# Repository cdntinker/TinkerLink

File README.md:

# Theory of operation:
* Power source is connected to USB1
  * can be populated with USB-C female or USB-A male
* USB2 can have its power turned on/off by the MCU using io12
  * can be populated with USB-C male or female
* D+ & D1, of course, pass right through
* When using USB-C on both ends, CC1 & CC2 are pased through (but swapped) and should allow for USB-PD capabilities
  * Also: R9 & R10 are there to add 5k1 resistors if needed.
    * Now the ESP handles inserting them via io2...
* LED1 is an RGB addressible LED (on io14) for status indication
  * RGBW now... Austin's fault... Blame Austin
* SW1 is on io13 of the MCU and can be used for local control

# Power Monitoring thoughts:
* INA chip selection
* The following are all drop-in replacements for each other...
  * INA228 (Current chip in the design)
    * very expensive
    * 625uA resoluation
  * INA237
    * 1/3 the price
    * 800uA resoluation
  * INA226
    * under a buck...
    * 1.5mA resoluation

# Firmware:
* Yet to be developped...
* Might work with TasmOTA like the original SiniLink could

# Notes:
Thanks to DJ_Dichotomy in the SuperHouseTV Discord for the antenna model...

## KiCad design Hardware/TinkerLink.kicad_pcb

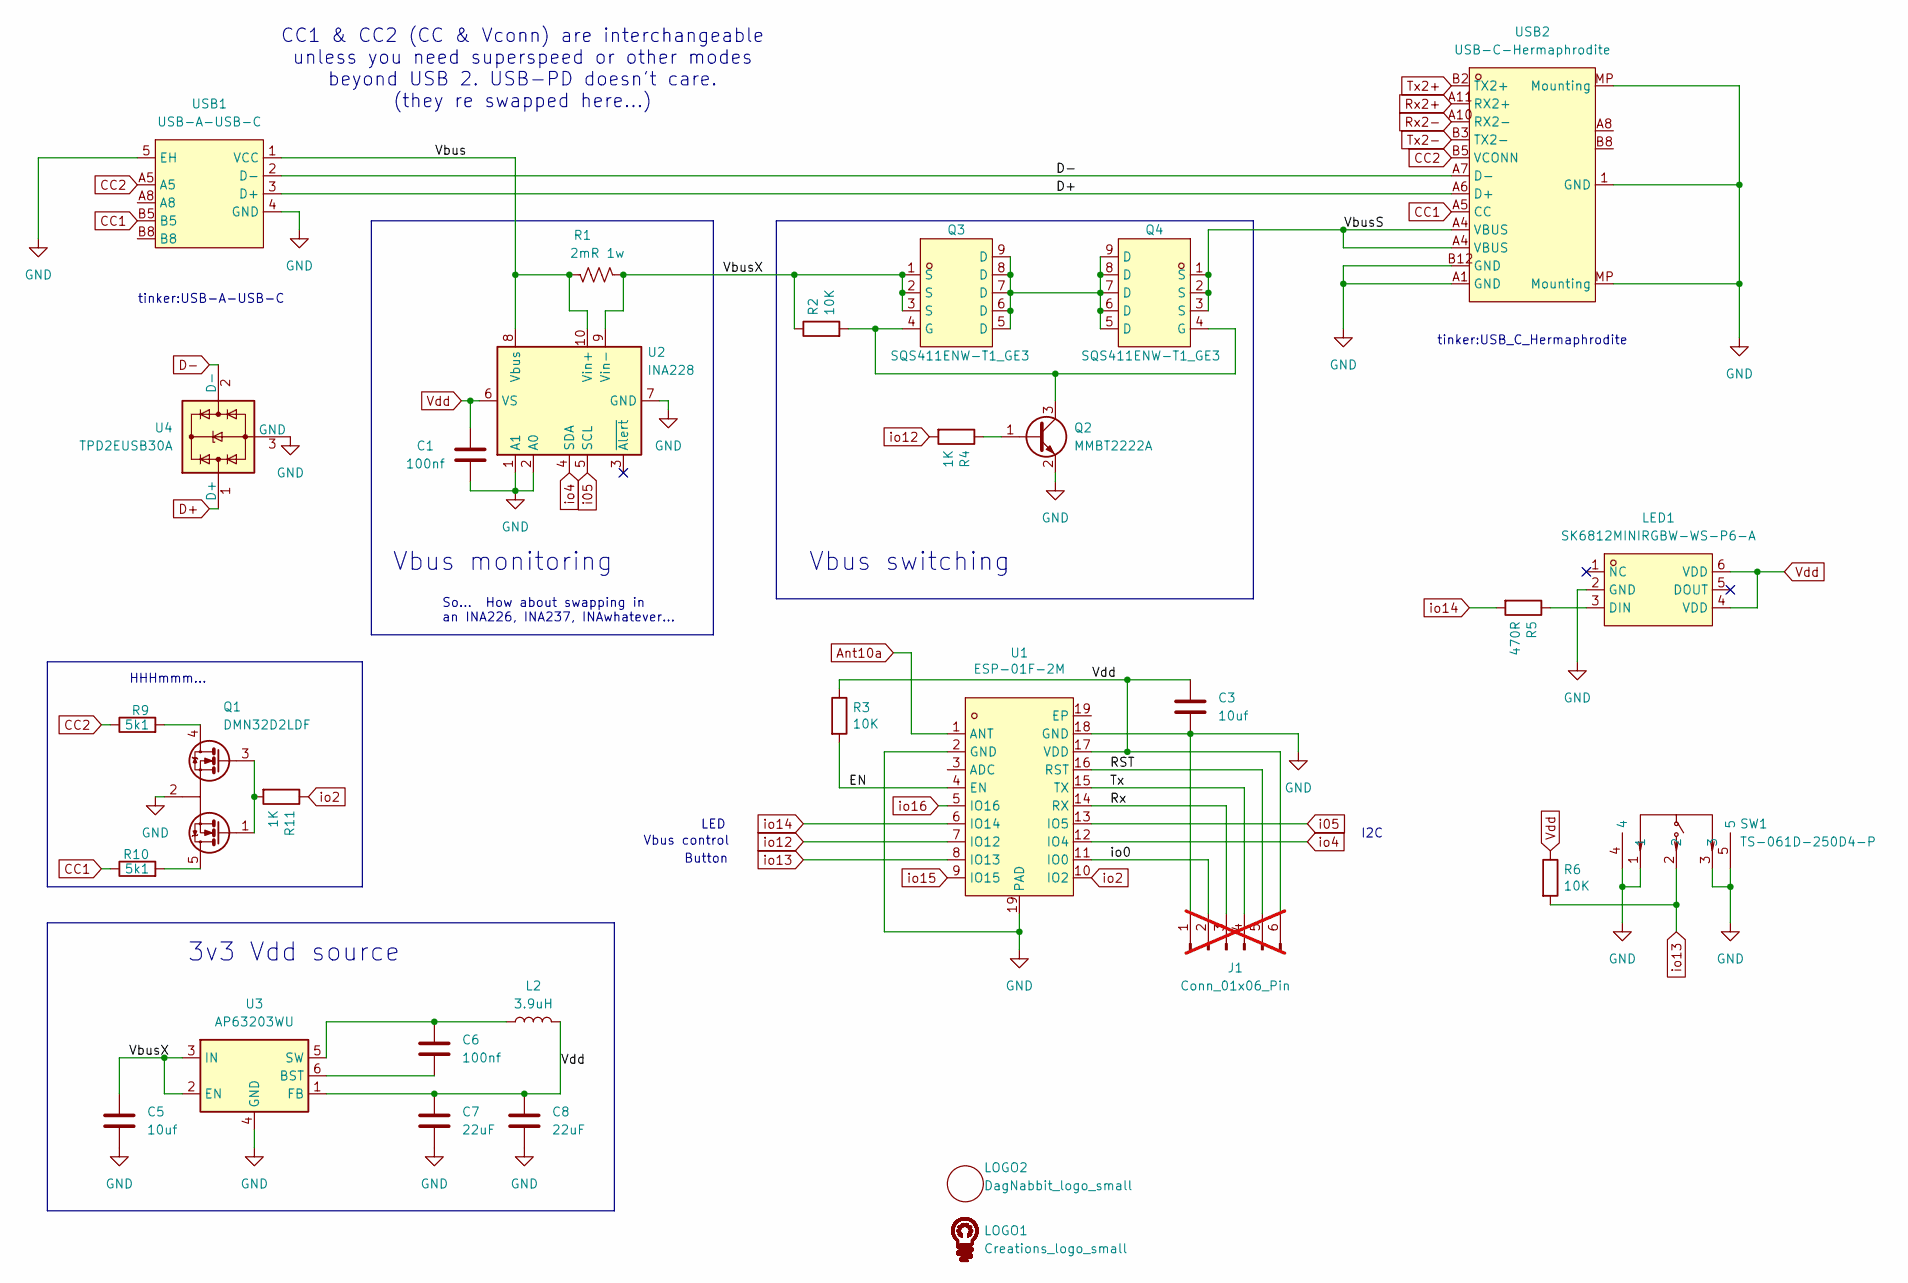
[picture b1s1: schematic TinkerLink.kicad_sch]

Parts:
C1: 100nf; C_0603_1608Metric; LCSC Part C14663
C3, C5: 10uf; C_0603_1608Metric; LCSC Part C19702
C6: 100nf; C_0603_1608Metric
C7, C8: 22uF; C_0603_1608Metric; LCSC Part C20416425
J1: Conn_01x06_Pin; ProgHeader_1x06_P2.00mm; not fitted
L2: 3.9uH; L_0603_1608Metric; LCSC Part C252079
LED1: SK6812MINIRGBW-WS-P6-A; LED-SMD_6P-L3.5-W3.5_SK6812MINIRGBW-WS-P6-A; MPN SK6812MINIRGBW-WS-P6-A; LCSC Part C7423106
LOGO1: Creations_logo_small; Creations logo small
LOGO2: DagNabbit_logo_small; DagNabbit
Q1: DMN32D2LDF; SOT-353_SC-70-5; LCSC Part C672154
Q2: MMBT2222A; SOT-23; LCSC Part C916372
Q3, Q4: SQS411ENW-T1_GE3; POWERPAK-1212-8_L3.1-W3.1-P0.65-LS3.3-BL; MPN SQS411ENW-T1_GE3; LCSC Part C3279469
R1: 2mR 1w; R_1206_3216Metric; LCSC Part C710257
R2, R3, R6: 10K; R_0603_1608Metric; LCSC Part C98220
R4, R11: 1K; R_0603_1608Metric; LCSC Part C22548
R5: 470R; R_0603_1608Metric; LCSC Part C114433
R9, R10: 5k1; R_0603_1608Metric; LCSC Part C23186
SW1: TS-061D-250D4-P; SW-SMD_K2-1847DT-A4SA-01; MPN TS-061D-250D4-P; LCSC Part C53207951
U1: ESP-01F-2M; ESP-01F; MPN ESP-01F-2M; LCSC Part C2764054
U2: INA228; VSSOP-10_3x3mm_P0.5mm; LCSC Part C2887910
U3: AP63203WU; TSOT-23-6; LCSC Part C780769
U4: TPD2EUSB30A; Texas_DRT-3; LCSC Part C3011197
USB1: USB-A-USB-C; MPN USB-212-BCW; LCSC Part C720521
USB2: USB-C-Hermaphrodite; USB_C_Hermaphrodite; MPN TYPE-C-31-G-10; LCSC Part C5370430

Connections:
/EN: R3.2, U1.4 (EN)
/RST: J1.5, U1.16 (RST)
/Rx: J1.3, U1.14 (RX)
/Tx: J1.4, U1.15 (TX)
/Vbus: R1.2, U2.8 (Vbus), U2.10 (Vin+), USB1.1 (VCC)
/VbusS: Q4.1 (S), Q4.2 (S), Q4.3 (S), USB2.A4 (VBUS)
/VbusX: C5.1, Q3.1 (S), Q3.2 (S), Q3.3 (S), R1.1, R2.1, U2.9 (Vin-), U3.2 (EN), U3.3 (IN)
/io0: J1.2, U1.11 (IO0)
Ant10a: U1.1 (ANT)
CC1: R10.1, USB1.B5, USB2.A5 (CC)
CC2: R9.1, USB1.A5, USB2.B5 (VCONN)
D+: U4.1 (D+), USB1.3 (D+), USB2.A6 (D+)
D-: U4.2 (D-), USB1.2 (D-), USB2.A7 (D-)
GND: C1.2, C3.2, C5.2, C7.2, C8.2, J1.1, LED1.2 (GND), Q1.2 (S), Q2.2 (E), SW1.1, SW1.3, SW1.4, SW1.5, U1.2 (GND), U1.18 (GND), U1.19 (PAD), U2.1 (A1), U2.2 (A0), U2.7 (GND), U3.4 (GND), U4.3 (GND), USB1.4 (GND), USB1.5 (EH), USB2.1 (GND), USB2.A1 (GND), USB2.B12 (GND), USB2.MP (Mounting)
unnamed: LED1.3 (DIN), R5.1
unnamed: Q1.5 (D1), R10.2
unnamed: Q1.4 (D2), R9.2
unnamed: Q1.1 (G1), Q1.3 (G2), R11.2
unnamed: Q2.1 (B), R4.1
unnamed: Q2.3 (C), Q3.4 (G), Q4.4 (G), R2.2
unnamed: Q3.5 (D), Q3.6 (D), Q3.7 (D), Q3.8 (D), Q3.9 (D), Q4.5 (D), Q4.6 (D), Q4.7 (D), Q4.8 (D), Q4.9 (D)
unnamed: C6.2, U3.6 (BST)
unnamed: C6.1, L2.1, U3.5 (SW)
Rx2+: USB2.A11 (RX2+)
Rx2-: USB2.A10 (RX2-)
Tx2+: USB2.B2 (TX2+)
Tx2-: USB2.B3 (TX2-)
Vdd: C1.1, C3.1, C7.1, C8.1, J1.6, L2.2, LED1.4 (VDD), LED1.6 (VDD), R3.1, R6.1, U1.17 (VDD), U2.6 (VS), U3.1 (FB)
i05: U1.13 (IO5), U2.5 (SCL)
io2: R11.1, U1.10 (IO2)
io4: U1.12 (IO4), U2.4 (SDA)
io12: R4.2, U1.7 (IO12)
io13: R6.2, SW1.2, U1.8 (IO13)
io14: R5.2, U1.6 (IO14)
io15: U1.9 (IO15)
io16: U1.5 (IO16)

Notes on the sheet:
HHHmmm...
tinker:USB-A-USB-C
Button
LED
So... How about swapping in an INA226, INA237, INAwhatever...
CC1 & CC2 (CC & Vconn) are interchangeable unless you need superspeed or other modes beyond USB 2. USB-PD doesn't care. (they re swapped here...)
Vbus monitoring
Vbus switching
3v3 Vdd source
tinker:USB_C_Hermaphrodite
I2C
Vbus control

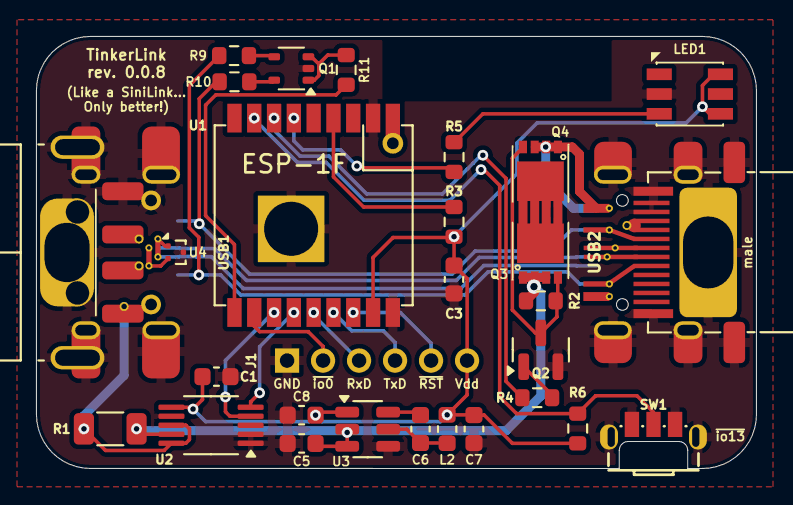
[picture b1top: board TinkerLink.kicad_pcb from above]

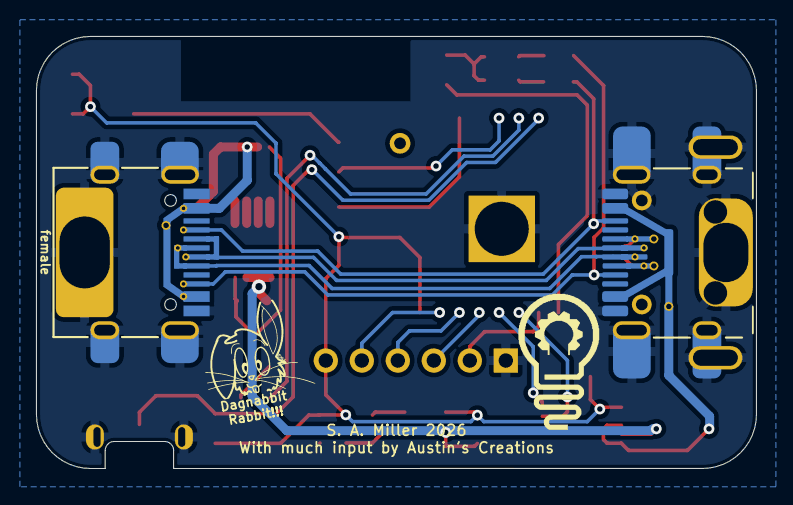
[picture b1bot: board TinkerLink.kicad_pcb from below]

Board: 2 copper layers, 40.0 x 24.0 mm, 31 parts (2 on the bottom side), 29 nets.
